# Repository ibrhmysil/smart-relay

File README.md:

# ESP8266 Based Smart Relay Module
Spesifications:
- ESP8266 Microcontroller
- 2x 5V DC Relay
- 5V to 3.3V Regulator
- IO Pins
- Reset and Boot Buttons
- Programable On Board LED
- 70x35 mm Dimensions

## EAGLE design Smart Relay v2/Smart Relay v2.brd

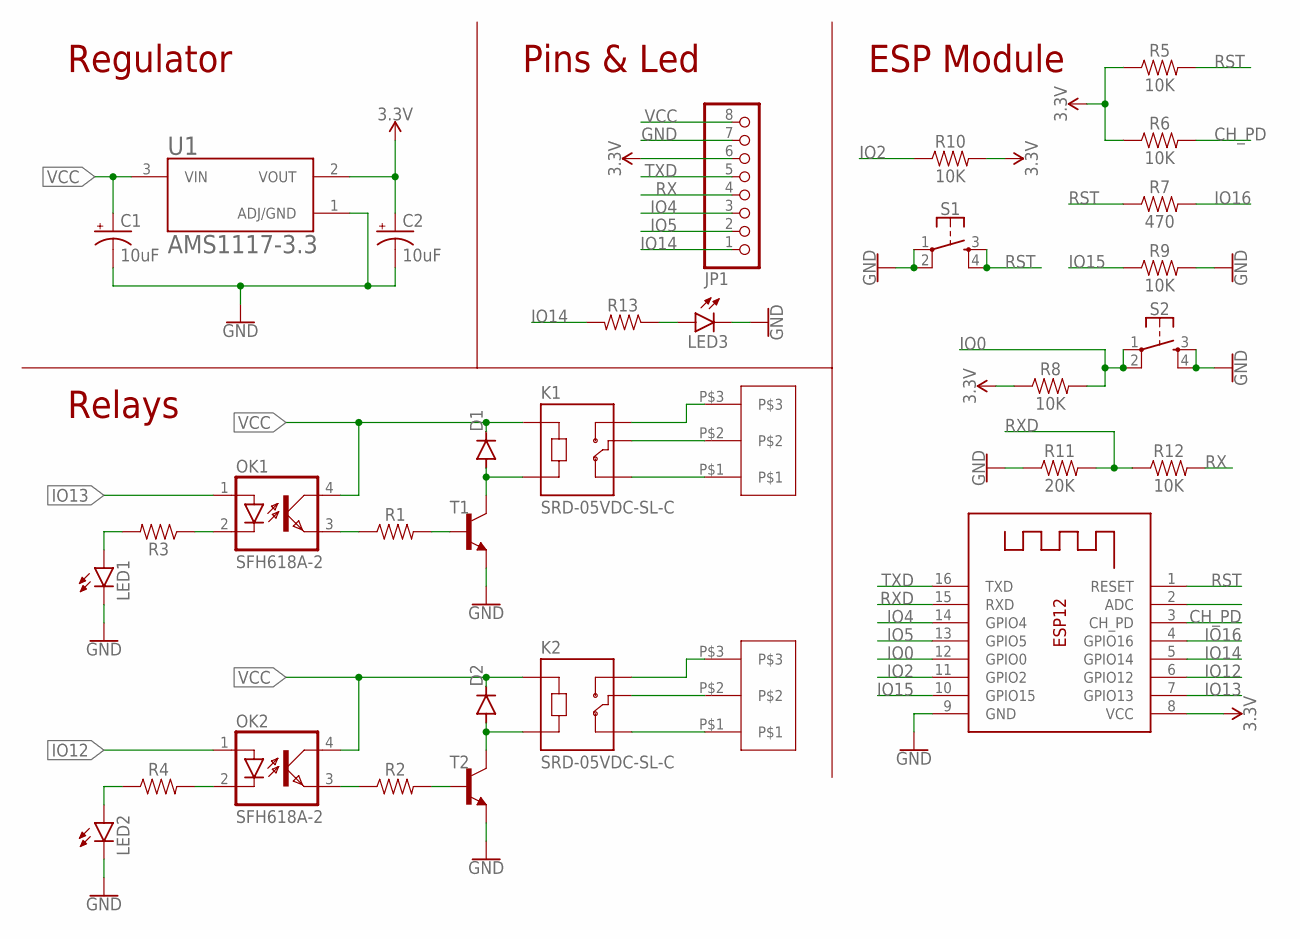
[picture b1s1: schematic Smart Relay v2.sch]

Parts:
C1, C2: 10uF; EIA3216
D1, D2: DIODE-SOD80C; SOD80C
JP1: PINHD-1X8; 1X08
K1, K2: SRD-05VDC-SL-C; RELAY_SRD-05VDC-SL-C
LED1, LED2, LED3: LEDCHIPLED_0805; CHIPLED_0805
OK1, OK2: SFH618A-2; DIP4
R1, R2, R3, R4, R13: 0805
R5, R6, R8, R9, R10, R12: 10K; 0805
R7: 470; 0805
R11: 20K; 0805
S1, S2: MOMENTARY-SWITCH-SPST-2-SMD-5.2MM-TALL; TACTILE_SWITCH_SMD_5.2MM
T1, T2: BC817-NPN-SOT23-BEC; SOT23-BEC
U1: AMS1117-3.3; SOT229P700X180-4N
U$1, U$2: 5MM_TERMINAL_3P
X1: ESP-12

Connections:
3.3V: C2.+, JP1.6, R5.1, R6.1, R8.1, R10.2, U1.2 (VOUT), X1.8 (VCC)
CH_PD: R6.2, X1.3 (CH_PD)
GND: C1.-, C2.-, JP1.7, LED1.C, LED2.C, LED3.C, R9.2, R11.1, S1.1, S1.2, S2.3, S2.4, T1.E, T2.E, U1.1 (ADJ/GND), X1.9 (GND)
IO0: R8.2, S2.1, S2.2, X1.12 (GPIO0)
IO2: R10.1, X1.11 (GPIO2)
IO4: JP1.3, X1.14 (GPIO4)
IO5: JP1.2, X1.13 (GPIO5)
IO12: OK2.1 (A), X1.6 (GPIO12)
IO13: OK1.1 (A), X1.7 (GPIO13)
IO14: JP1.1, R13.2, X1.5 (GPIO14)
IO15: R9.1, X1.10 (GPIO15)
IO16: R7.2, X1.4 (GPIO16)
unnamed: LED3.A, R13.1
unnamed: K2.NC, U$2.P$1
unnamed: D1.A, K1.A2, T1.C
unnamed: K2.COM, U$2.P$2
unnamed: D2.A, K2.A2, T2.C
unnamed: R2.2, T2.B
unnamed: OK2.3 (EMIT), R2.1
unnamed: LED2.A, R4.1
unnamed: OK2.2 (C), R4.2
unnamed: OK1.3 (EMIT), R1.1
unnamed: R1.2, T1.B
unnamed: LED1.A, R3.2
unnamed: OK1.2 (C), R3.1
unnamed: K2.NO, U$2.P$3
unnamed: K1.NC, U$1.P$1
unnamed: K1.COM, U$1.P$2
unnamed: K1.NO, U$1.P$3
RST: R5.2, R7.1, S1.3, S1.4, X1.1 (RESET)
RX: JP1.4, R12.2
RXD: R11.2, R12.1, X1.15 (RXD)
TXD: JP1.5, X1.16 (TXD)
VCC: C1.+, D1.C, D2.C, JP1.8, K1.A1, K2.A1, OK1.4 (COL), OK2.4 (COL), U1.3 (VIN)

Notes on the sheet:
Regulator
Pins & Led
Relays
ESP Module

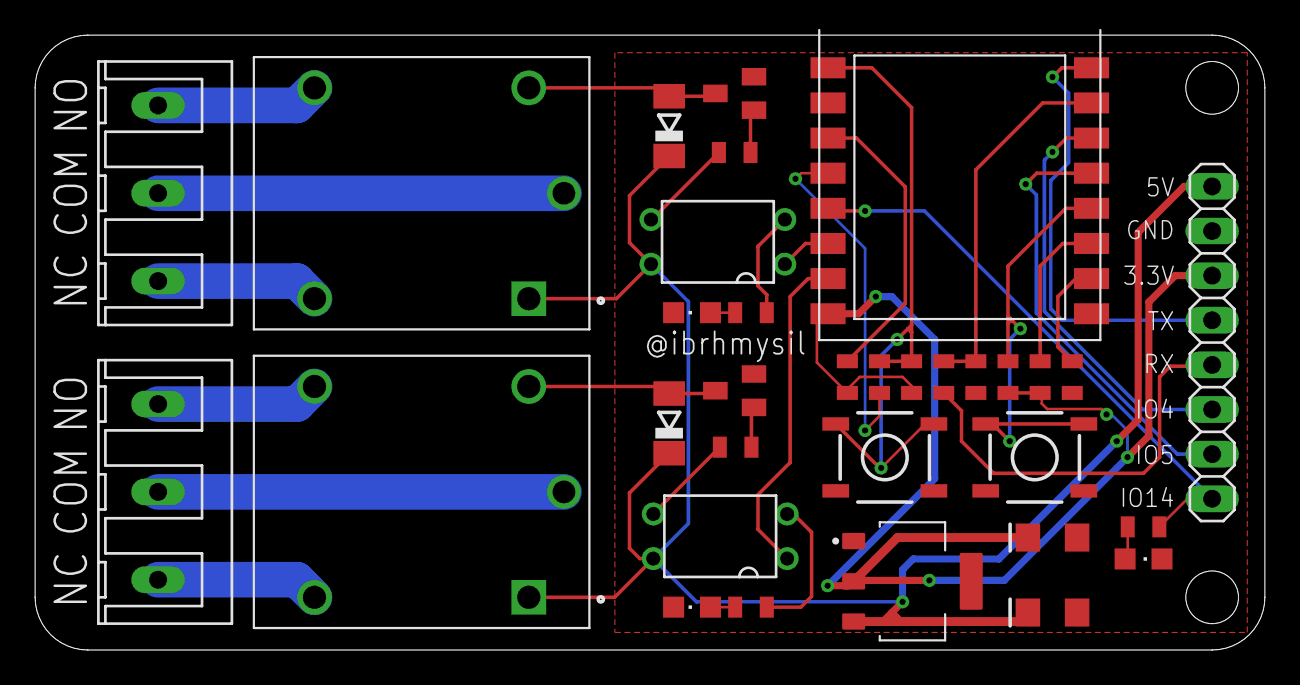
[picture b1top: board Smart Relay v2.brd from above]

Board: 2 copper layers, 70.0 x 35.0 mm, 33 parts (0 on the bottom side), 34 nets.

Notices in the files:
parts and their libraries:
SparkFun-Capacitors: Licensing: Creative Commons ShareAlike 4.0 International - https://creativecommons.org/licenses/by-sa/4.0
